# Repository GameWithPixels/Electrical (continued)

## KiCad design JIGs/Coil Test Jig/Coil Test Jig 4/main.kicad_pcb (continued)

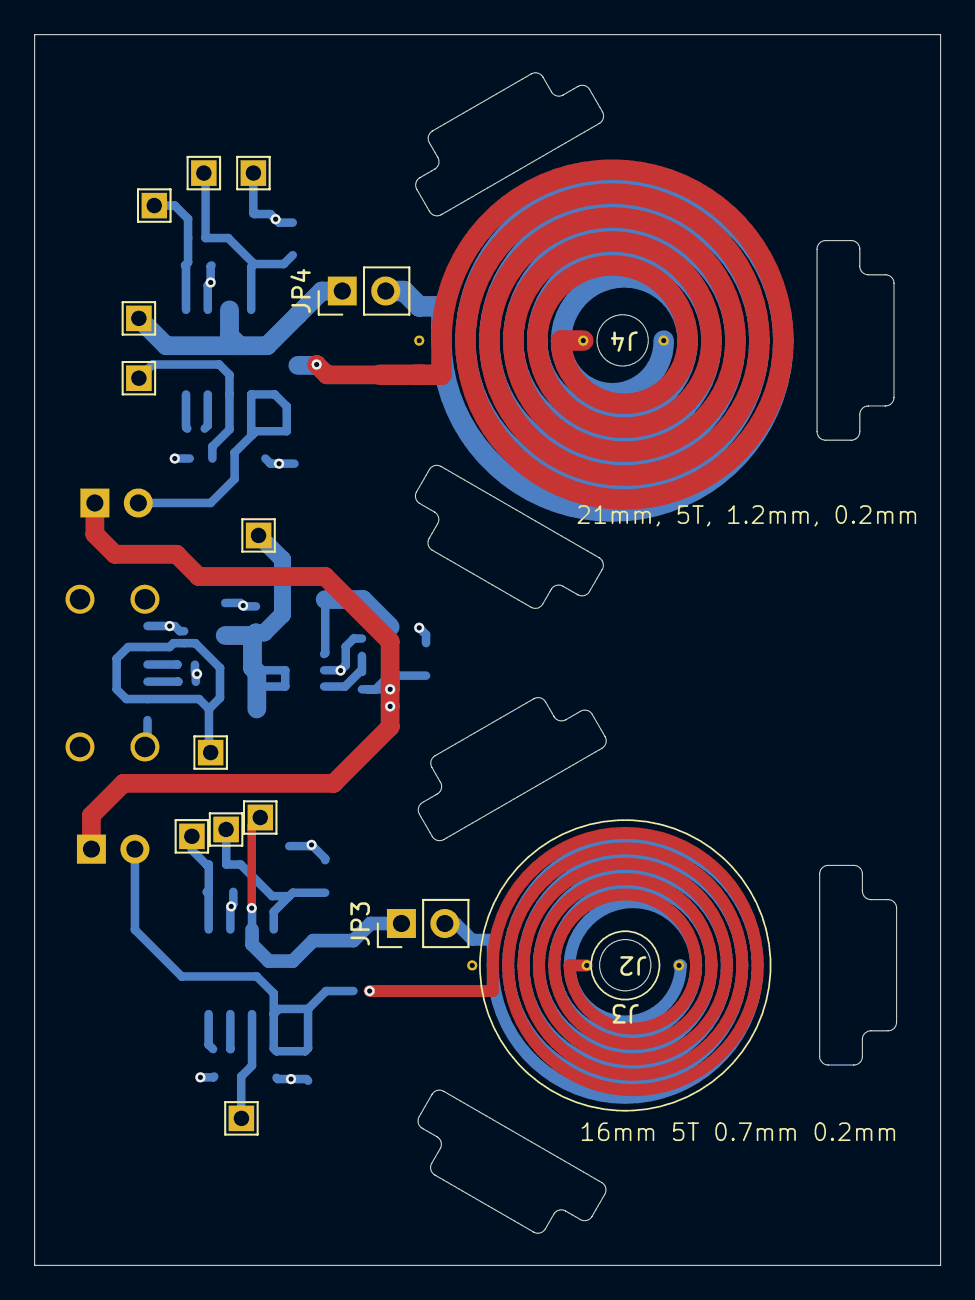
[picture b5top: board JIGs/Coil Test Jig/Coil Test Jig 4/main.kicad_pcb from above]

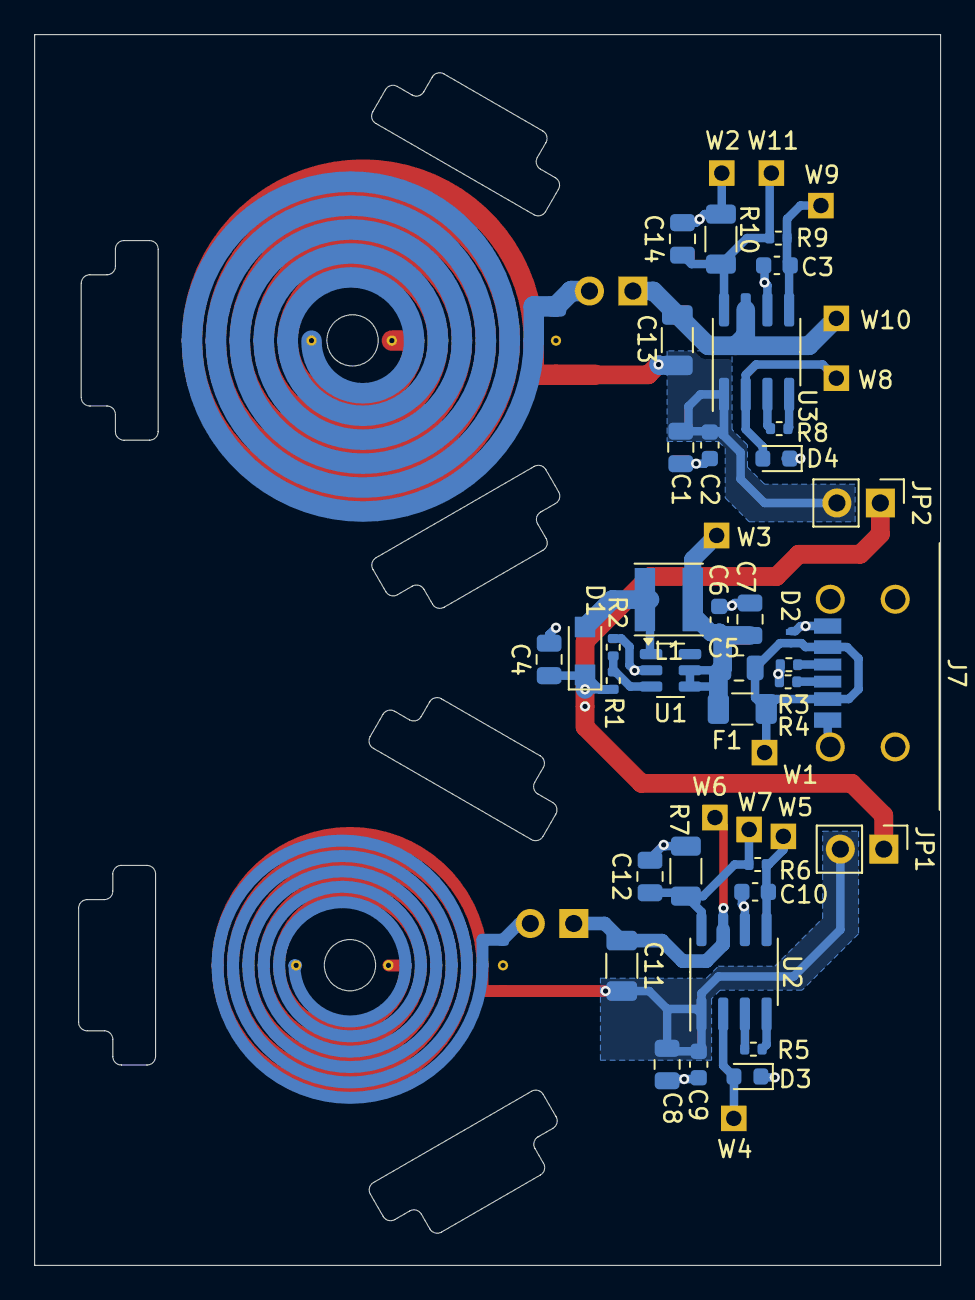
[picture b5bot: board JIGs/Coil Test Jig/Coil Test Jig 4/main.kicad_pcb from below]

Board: 4 copper layers, 53.0 x 72.0 mm, 52 parts (36 on the bottom side), 24 nets.

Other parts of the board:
J3: TX_Coil; TX Coil

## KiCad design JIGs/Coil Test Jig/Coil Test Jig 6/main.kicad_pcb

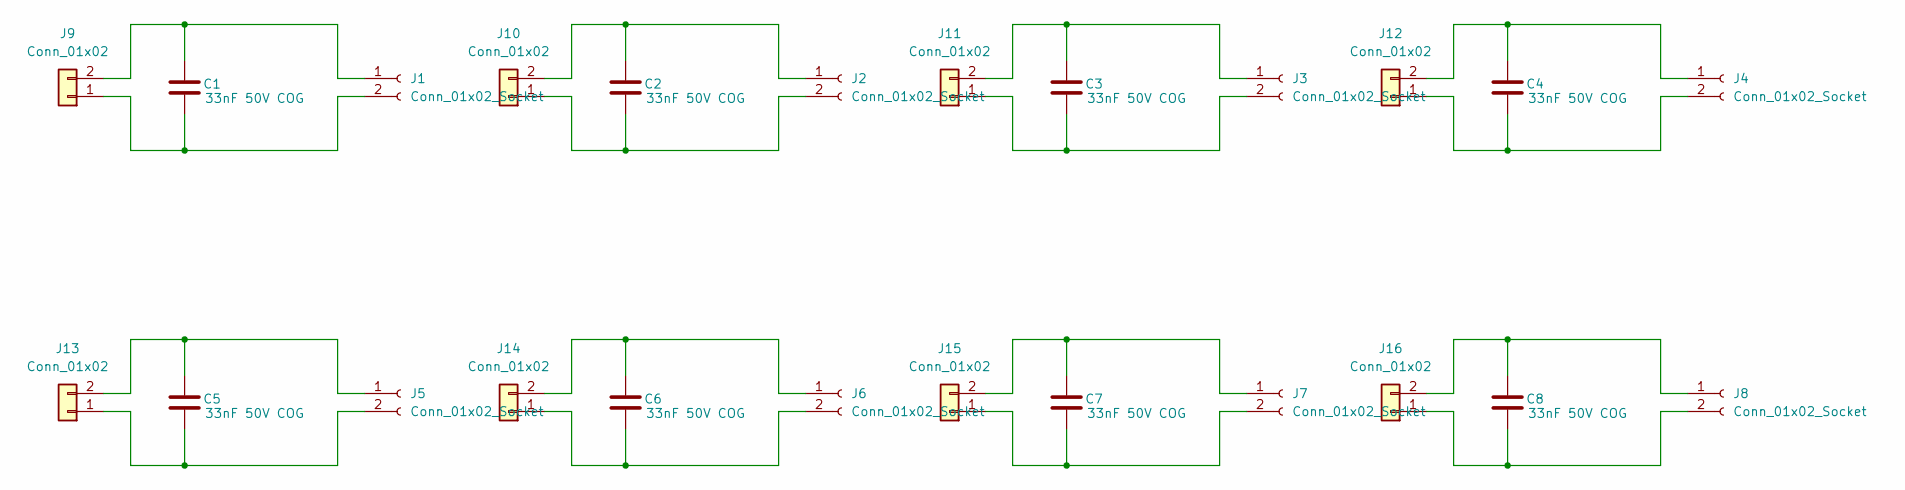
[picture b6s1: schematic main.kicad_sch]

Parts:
C1, C2, C3, C4, C5, C6, C7, C8: 33nF 50V COG; C_1206_3216Metric; Part Number GRM3195C1H333JA01D; LCSC Part Number C97930
J1, J2, J3, J4, J5, J6, J7, J8: Conn_01x02_Socket; Coil_Con
J9, J10, J11, J12, J13, J14, J15, J16: Conn_01x02; PinHeader_1x02_P2.54mm_Vertical

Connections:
unnamed: C1.2, J1.1, J9.2
unnamed: C1.1, J1.2, J9.1
unnamed: C2.1, J2.2, J10.1
unnamed: C2.2, J2.1, J10.2
unnamed: C3.1, J3.2, J11.1
unnamed: C3.2, J3.1, J11.2
unnamed: C4.1, J4.2, J12.1
unnamed: C4.2, J4.1, J12.2
unnamed: C5.1, J5.2, J13.1
unnamed: C5.2, J5.1, J13.2
unnamed: C6.1, J6.2, J14.1
unnamed: C6.2, J6.1, J14.2
unnamed: C7.1, J7.2, J15.1
unnamed: C7.2, J7.1, J15.2
unnamed: C8.1, J8.2, J16.1
unnamed: C8.2, J8.1, J16.2

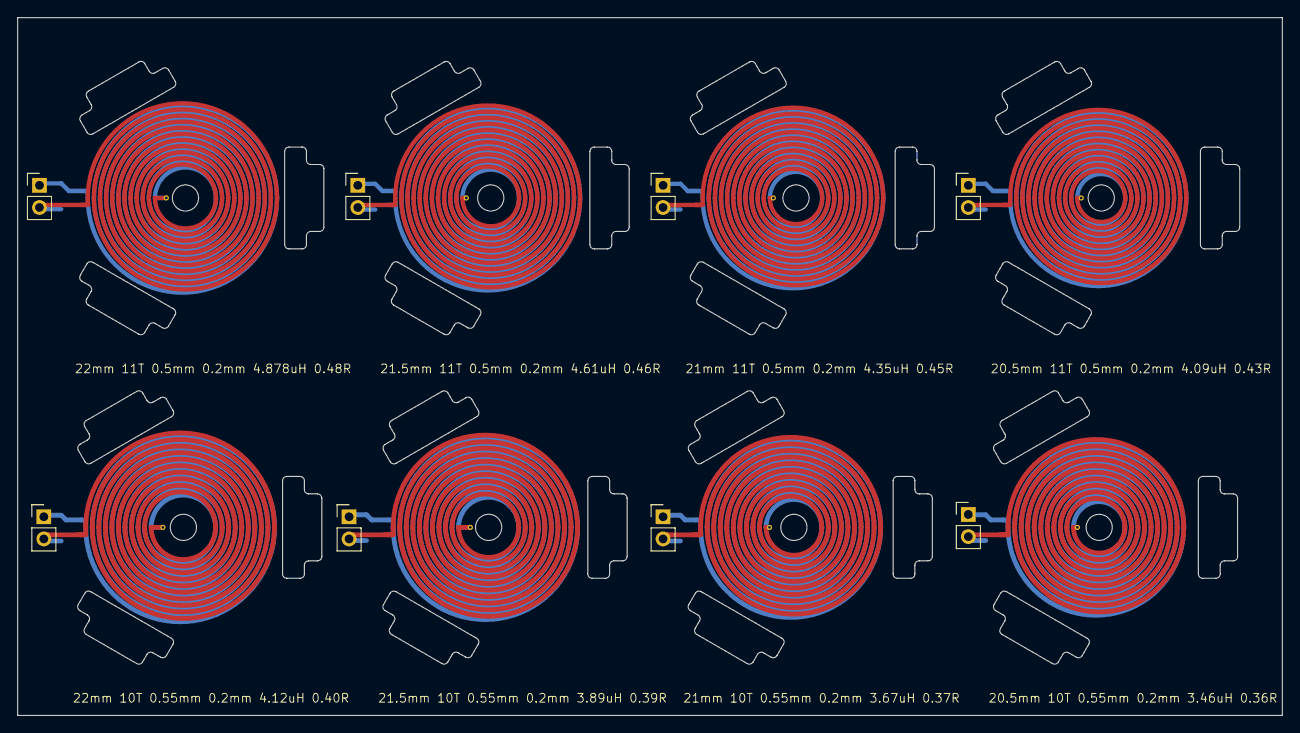
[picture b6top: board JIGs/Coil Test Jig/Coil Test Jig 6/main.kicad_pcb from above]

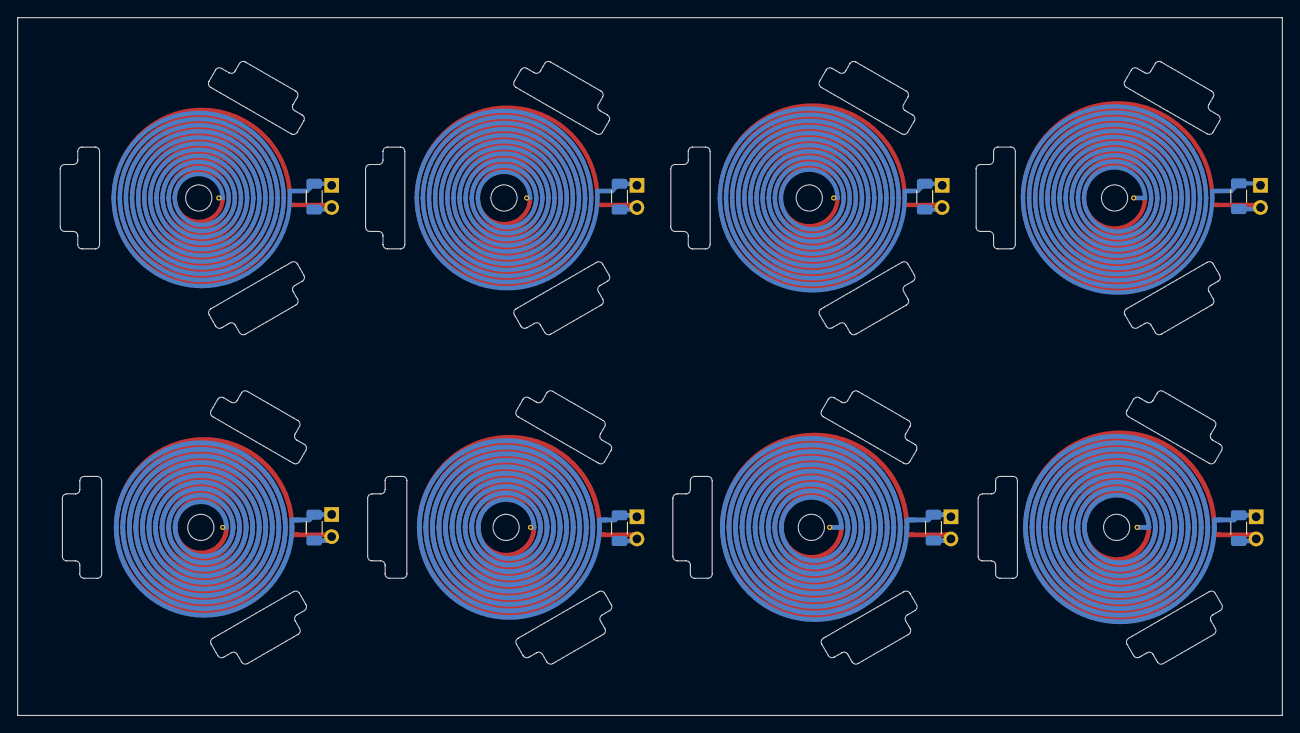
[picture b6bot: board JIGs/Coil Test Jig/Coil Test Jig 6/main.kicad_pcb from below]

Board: 2 copper layers, 145.0 x 80.0 mm, 24 parts (8 on the bottom side), 16 nets.
